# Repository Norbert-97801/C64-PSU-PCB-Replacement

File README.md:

# C64-PSU-PCB-Replacement

## PSU PCB Replacement for the Commodore C64 PSU 902503-06

 Here is my soloution for the C64 Power Supply Unit probelm when the Power Supply Unit is going to fail or it's too old. I've developed a Power Supply Unit PCB to replace the original PCB. The build in 7805 will be used as a mounting point to install the new PCB in the Transformer housing. The new PCB is using an adjustable DC/DC Converter to get the 5.1V and there is up to 10 watts of power left that doesn't converted into heat anymore.

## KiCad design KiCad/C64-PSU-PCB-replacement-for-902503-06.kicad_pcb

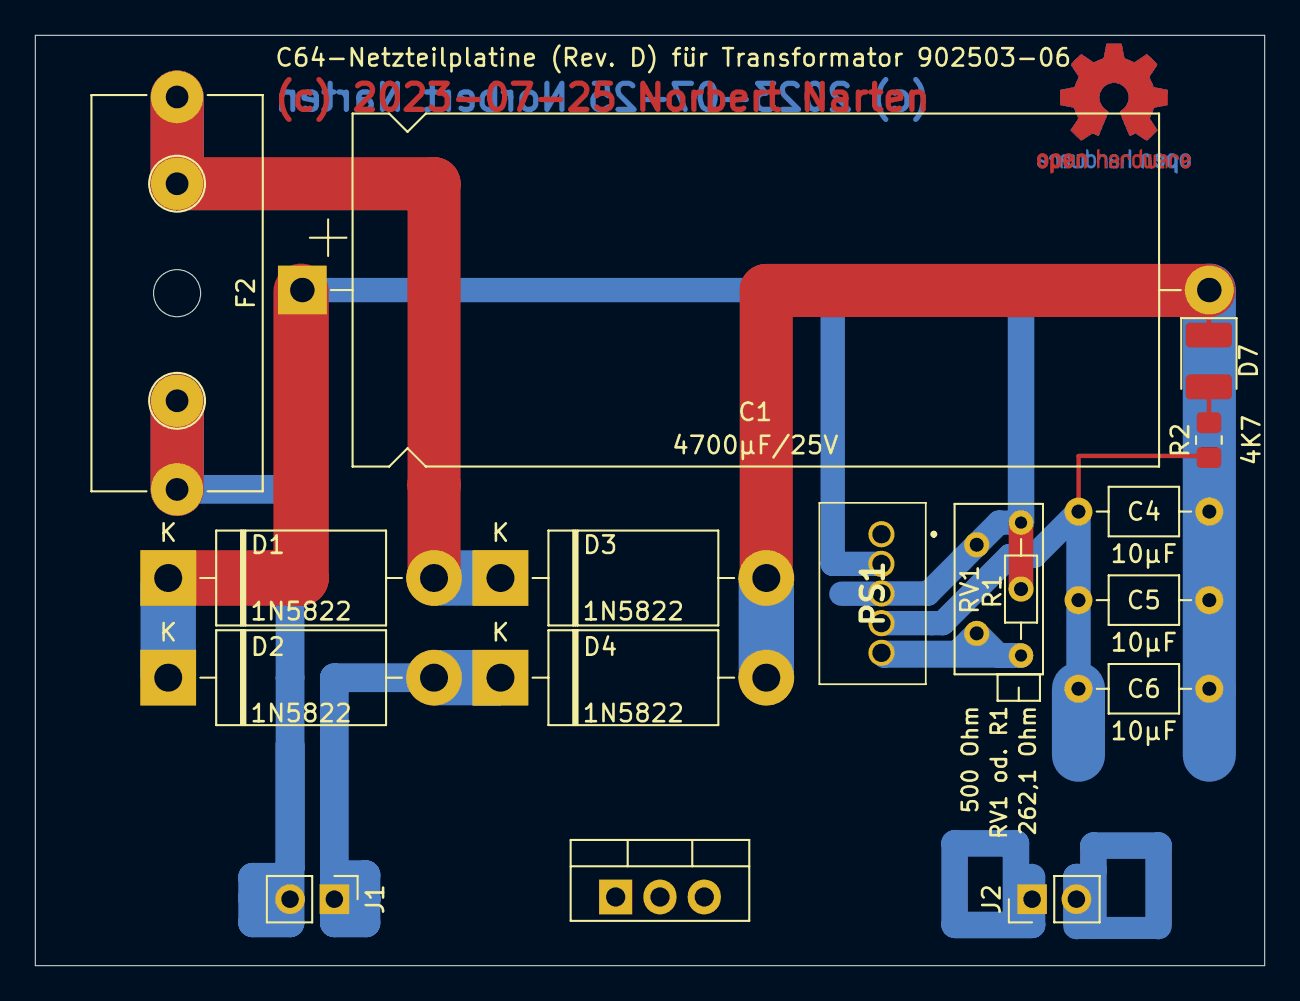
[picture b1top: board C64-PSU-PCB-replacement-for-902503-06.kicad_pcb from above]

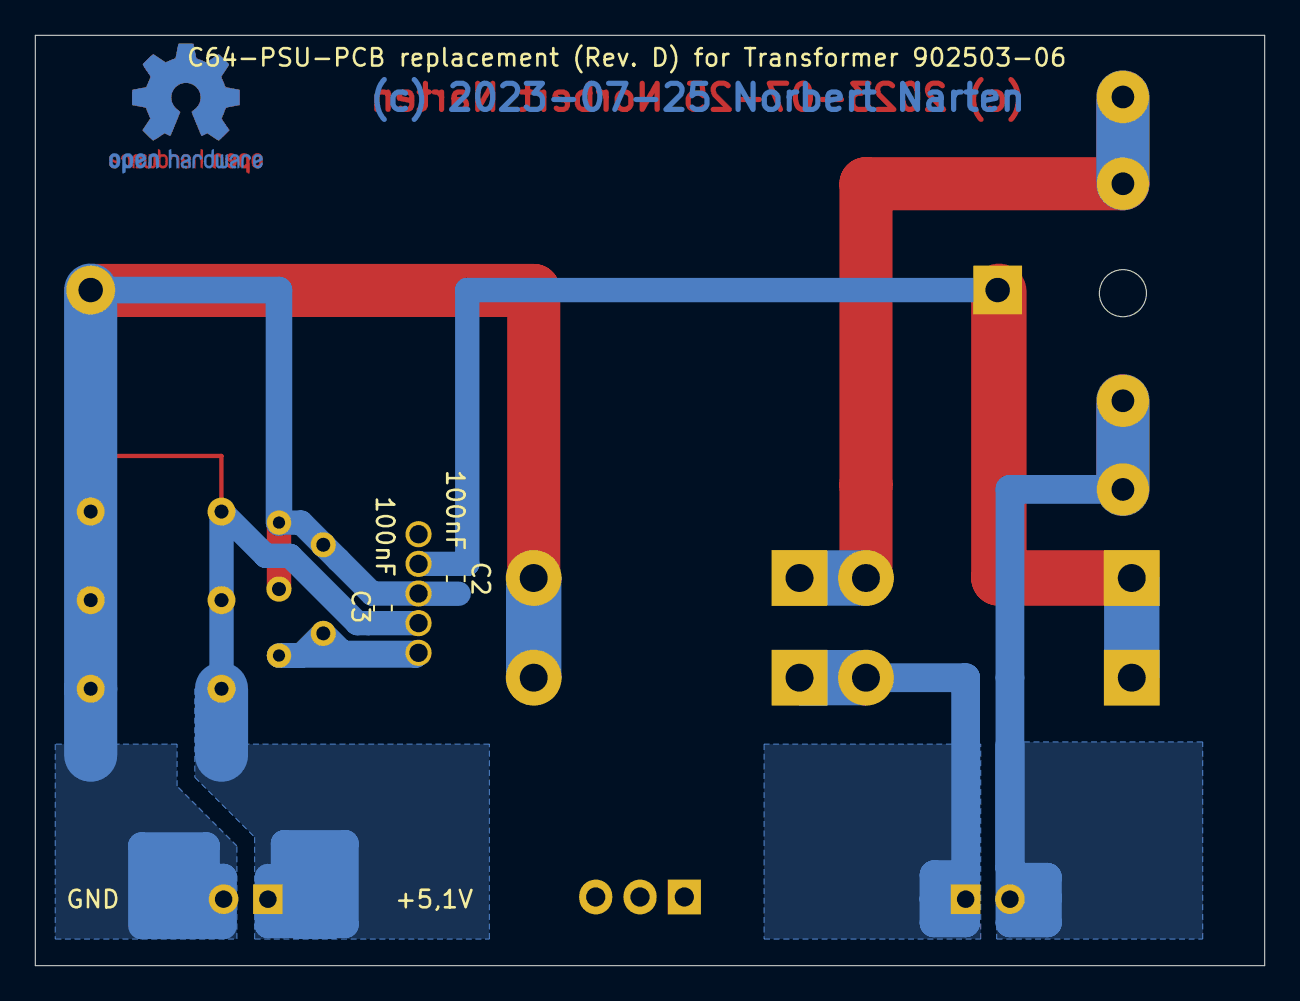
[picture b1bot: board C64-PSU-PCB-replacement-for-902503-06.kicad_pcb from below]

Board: 2 copper layers, 70.5 x 53.3 mm, 23 parts (4 on the bottom side), 8 nets.

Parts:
+5.1V: SolderWirePad_1x01_SMD_5x10mm
C1: 4700µF/25V; CP_Axial_L46.0mm_D20.0mm_P52.00mm_Horizontal
C2, C3: 100nF; C_0603_1608Metric_Pad1.08x0.95mm_HandSolder
C4, C5, C6: 10µF; C_Axial_L3.8mm_D2.6mm_P7.50mm_Horizontal
D1, D2, D3, D4: 1N5822; D_DO-201AD_P15.24mm_Horizontal
D7: LED; D_1210_3225Metric_Pad1.42x2.65mm_HandSolder
F2: Fuse; Fuseholder_Cylinder-5x20mm_Schurter_0031_8201_Horizontal_Op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
GND: SolderWirePad_1x01_SMD_5x10mm
J1: 7V-12V AC; PinHeader_1x02_P2.54mm_Vertical
J2: 5,1V DC; PinHeader_1x02_P2.54mm_Vertical
J3, J4: F-Mount; Pin_D1.3mm_L11.0mm
PS1: OKR-T3-W12-C; OKRT15W12C
R1: 262,1 Ohm; R_Axial_DIN0204_L3.6mm_D1.6mm_P7.62mm_Horizontal
R2: 4K7; R_0805_2012Metric_Pad1.20x1.40mm_HandSolder
RV1: 500 Ohm; Potentiometer_Bourns_3296Z_Horizontal
U0: TO220_for_install; TO-220-3_Vertical

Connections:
/+5,1V: +5.1V.1, C3.2, C4.1, C5.1, C6.1, J2.1, PS1.4 (+VOUT), R2.1
/+16V: C1.1, C2.1, D1.1 (K), D2.1 (K), PS1.2 (+VIN)
GND: C1.2, C2.2, C3.1, C4.2, C5.2, C6.2, D3.2 (A), D4.2 (A), D7.1 (K), GND.1, J2.2, PS1.3 (GND_(COMMON)), R1.2, RV1.1, RV1.2
unnamed: D1.2 (A), D3.1 (K), F2.2
unnamed: D2.2 (A), D4.1 (K), J1.1
unnamed: D7.2 (A), R2.2
unnamed: F2.1, J1.2, J3.1
unnamed: PS1.5 (TRIM), R1.1, RV1.3

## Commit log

2025-04-20 Create test

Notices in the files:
KiCad/C64-PSU-PCB-replacement-for-902503-06.kicad_pcb:
(c) 2023-07-25 Norbert Narten
